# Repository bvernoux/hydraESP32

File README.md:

# hydraESP32

HydraESP32 HydraBus v1.0 Shield for ESP-WROOM-32 V1.1 Rev1.0 (Tested) 

https://oshpark.com/shared_projects/dgKJqznH

HydraBus Shield / Breakout board for ESP-WROOM-32 or ESP-32S.

This shield can be used with or without HydraBus board, you can even cut HydraBus specific right side (on the line) to have a tiny ESP-WROOM-32 breakout board.

It is not mandatory to solder the components on this shield in order to use it, you will just need to connect +3v3 on VCC Pin header 

* New features versus previous version [V1.0 Rev1.1](https://oshpark.com/shared_projects/6t5hURXL):
   * Added LDO (TPS73633DBVR SOT23-5) to convert 5V(VUSB) to a clean VCC (+3.3v) for ESP32 and which can be enabled by an HydraBus Pin or  with a JUMPER on J7 (which connect +3.3V from HydraBus to EN of the LDO)
   * Added VCC connector in order to measure ESP32 current/power consumption (if not used to measure current just add a JUMPER on VCC to power the ESP32)
   * Added J6 connector to have access to ESP32 SPI FLASH IOs (now all pins are available)

* This shield can be used only on bottom of HydraBus board (in order to use other shields on top of HydraBus)

* The [HydraBus board](http://hydrabus.com/hydrabus-1-0-specifications/) is a small (60mm x 37mm) and [low cost](http://hydrabus.com/buy-online/), multi-tool extensible board with STM32F405 Cortex M4F 32bits MCU @168MHz with a fully open source firmware [hydrafw](https://github.com/bvernoux/hydrafw) and full online documentation [hydrafw wiki](https://github.com/bvernoux/hydrafw/wiki)

* The ESP-WROOM-32 is a low-power 32-bit 240 MHz dual core MCU Wi-
Fi+BLE combo module that highly integrates TCP/IP network stacks, 12-
bit ADC and HSPI/SDIO/UART/PWM/I2C/I2S interfaces.
See [ESP32 Overview](http://www.espressif.com/en/products/hardware/esp32/overview), [ESP-WROOM-32 link/info](https://espressif.com/en/producttype/esp-wroom-32), [Espressif Products Overview including ESP-WROOM-32 PDF](http://www.elinistech.com/images/esp8266/Espressif%20Introduction-EN.pdf)

* Design based on official [esp_wroom_32_datasheet_en.pdf (September 26, 2016)](https://espressif.com/sites/default/files/documentation/esp_wroom_32_datasheet_en.pdf)

BOM:

| Qty | Value | Device | Package | Parts | Description |
|------|----------|------------|-------------|---------|------------------|
| 1   | -        | ESP_WROOM_32 or ESP-32S        | ESP-WROOM-32 or ESP-32S          | U1        | Espressif ESP-WROOM-32 or ESP-32S Module    |
| 1   | -        | TPS73633 | SOT23-5L              | U2        | Texas Instrument LDO             |
| 1   | 2.2uF    | CAPACITOR_NPOL-0603 | C603                  | C1        | SMD Non-Polarized capacitor          |
| 1   | 1uF      | CAPACITOR_NPOL-0603 | C603                  | C2        | SMD Non-Polarized capacitor          |
| 2   | 100nF    | CAPACITOR_NPOL-0603 | C603                  | C3, C4    | SMD Non-Polarized capacitor          |
| 2   | 10K      | RESISTOR-0603       | R603                  | R1, R2    | SMD Resistor                                 |
| 1   | -        |                     | HYDRABUS_SHIELD_M2X7  | J1        | 2x7 Pin header      |
| 4   | -        |                     | HYDRABUS_SHIELD_M2X10 |J2, J3, J4, J5    | 2x10 Pin header                  |
| 2   | -        |                     | HYDRABUS_SHIELD_M1X6  | J6, SWD_DEBUG | 1x6 Pin header |
| 2   | -        |                     | Jumper - 2 Pin  | J7, VCC   |  Jumper 2 Pin |
| 2   | -        |                     | CON_HEADER_1X02-PTH   | J7, VCC   | 1x2 Pin header |

Note1: LDO U2 can be also replaced by MIC5319-3.3YD5-TR (Microchip)

Note2: If you do not want to solder those components you can avoid them and directly connect HydraBus 3v3 to VCC Pin near J5 marking

For more details see also [HydraBus_1_0_Shield_ESP_WROOM_32_v1_1_Rev1_BOM.csv](HydraBus_1_0_Shield_ESP_WROOM_32_v1_1_Rev1_BOM.csv)

Tested with success with an ESP-32S Module from Ai-Thinker (it is recommended to use official Espressif ESP-WROOM-32)

HydraBus_1_0_Shield_ESP_WROOM_32_v1_1_Rev1_Top:
[HydraBus_1_0_Shield_ESP_WROOM_32_v1_1_Rev1_Top](HydraBus_1_0_Shield_ESP_WROOM_32_v1_1_Rev1_Top.png)

HydraBus_1_0_Shield_ESP_WROOM_32_v1_1_Rev1_Bottom:
[HydraBus_1_0_Shield_ESP_WROOM_32_v1_1_Rev1_Bottom](HydraBus_1_0_Shield_ESP_WROOM_32_v1_1_Rev1_Bottom.png)

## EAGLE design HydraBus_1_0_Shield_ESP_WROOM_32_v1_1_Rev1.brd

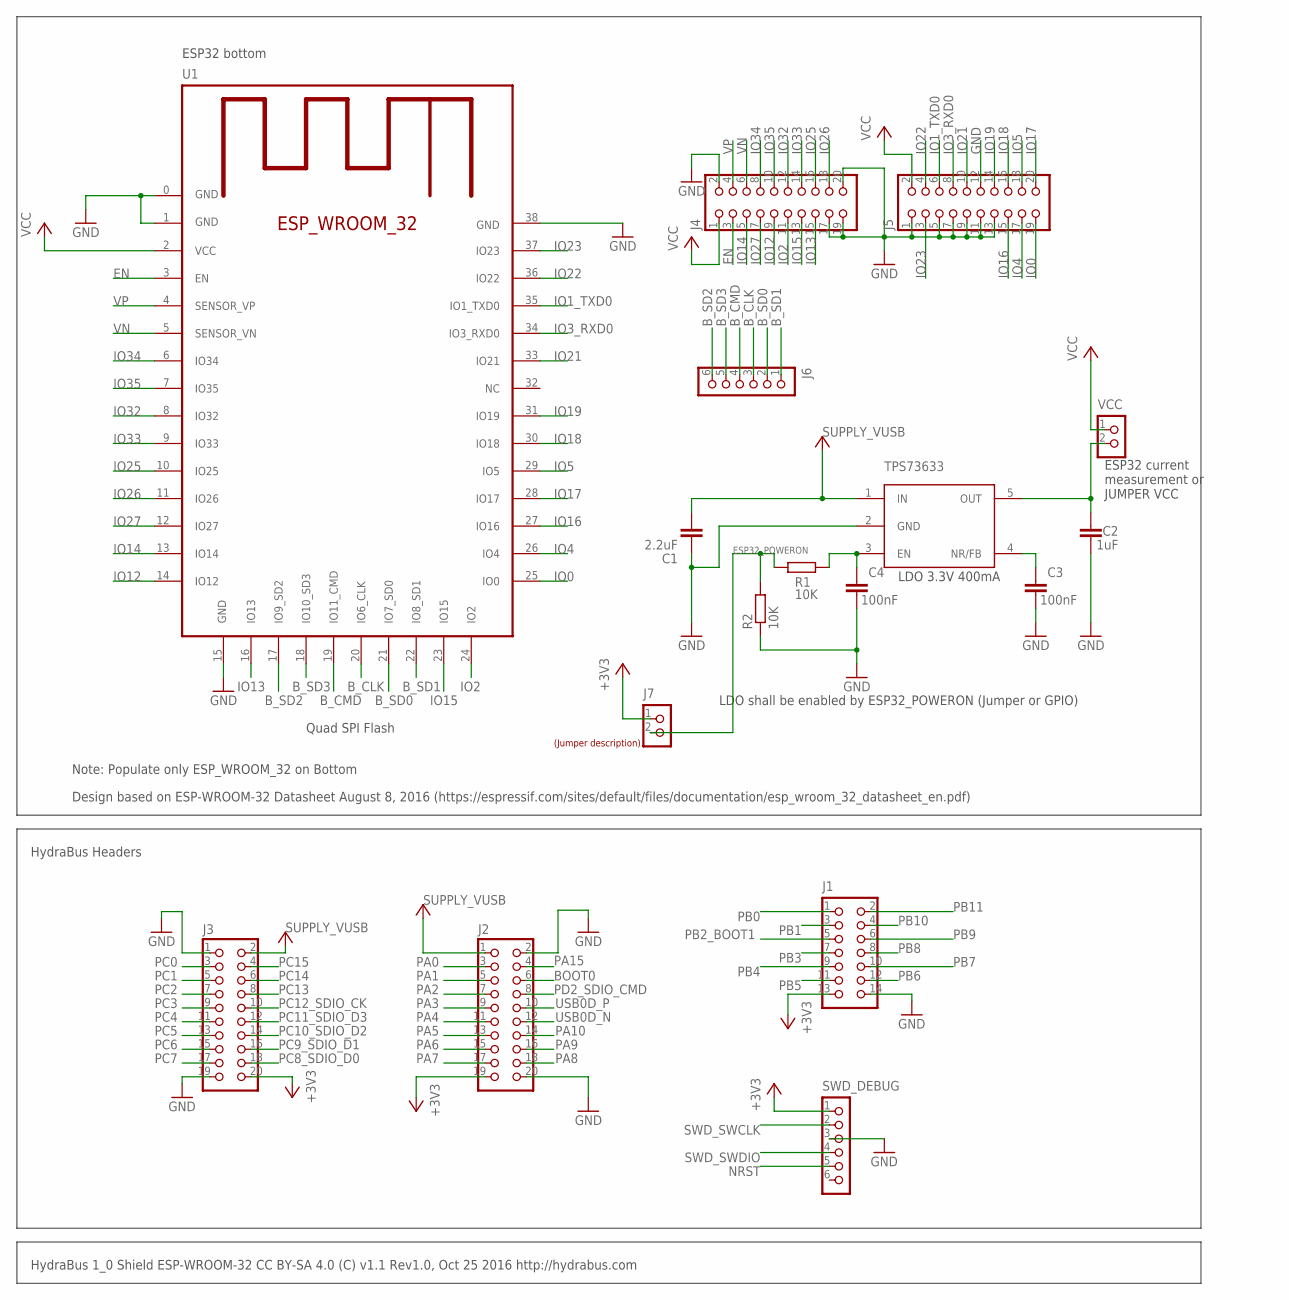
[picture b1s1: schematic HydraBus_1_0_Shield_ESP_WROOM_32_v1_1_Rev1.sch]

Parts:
C1: 2.2uF; C603
C2: 1uF; C603
C3, C4: 100nF; C603
J1: HYDRABUS_SHIELD_CON_HEADER_2X07_BOTTOM; HYDRABUS_SHIELD_M2X7_BOTTOM
J2, J3: HYDRABUS_SHIELD_CON_HEADER_2X10_BOTTOM; HYDRABUS_SHIELD_M2X10_BOTTOM
J4, J5: HYDRABUS_SHIELD_CON_HEADER_2X10; HYDRABUS_SHIELD_M2X10
J6: HYDRABUS_SHIELD_CON_HEADER_1X06; HYDRABUS_SHIELD_M1X6
J7: CON_HEADER_1X02-PTH; M1X2
R1, R2: 10K; R603
SWD_DEBUG: HYDRABUS_SHIELD_CON_HEADER_1X06_BOTTOM; HYDRABUS_SHIELD_M1X6_BOTTOM
U1: ESP_WROOM_32
U2: TPS73633; SOT23-5L
U$1: LABEL_JUMPER_1X2; JUMP2_DESC
VCC: CON_HEADER_1X02-PTH; M1X2

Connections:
+3V3: J1.13, J2.19, J3.20, J7.1, SWD_DEBUG.1
BOOT0: J2.6
B_CLK: J6.3, U1.20 (IO6_CLK)
B_CMD: J6.4, U1.19 (IO11_CMD)
B_SD0: J6.2, U1.21 (IO7_SD0)
B_SD1: J6.1, U1.22 (IO8_SD1)
B_SD2: J6.6, U1.17 (IO9_SD2)
B_SD3: J6.5, U1.18 (IO10_SD3)
EN: J4.3, U1.3 (EN)
ESP32_POWERON: J7.2, R1.1, R2.2
GND: C1.1, C2.1, C3.1, C4.1, J1.14, J2.2, J2.20, J3.1, J3.19, J4.2, J4.17, J4.19, J4.20, J5.1, J5.5, J5.7, J5.9, J5.11, J5.12, J5.13, R2.1, SWD_DEBUG.3, U1.0 (GND), U1.1 (GND), U1.15 (GND), U1.38 (GND), U2.2 (GND)
IO0: J5.19, U1.25 (IO0)
IO1_TXD0: J5.6, U1.35 (IO1_TXD0)
IO2: J4.11, U1.24 (IO2)
IO3_RXD0: J5.8, U1.34 (IO3_RXD0)
IO4: J5.17, U1.26 (IO4)
IO5: J5.18, U1.29 (IO5)
IO12: J4.9, U1.14 (IO12)
IO13: J4.15, U1.16 (IO13)
IO14: J4.5, U1.13 (IO14)
IO15: J4.13, U1.23 (IO15)
IO16: J5.15, U1.27 (IO16)
IO17: J5.20, U1.28 (IO17)
IO18: J5.16, U1.30 (IO18)
IO19: J5.14, U1.31 (IO19)
IO21: J5.10, U1.33 (IO21)
IO22: J5.4, U1.36 (IO22)
IO23: J5.3, U1.37 (IO23)
IO25: J4.16, U1.10 (IO25)
IO26: J4.18, U1.11 (IO26)
IO27: J4.7, U1.12 (IO27)
IO32: J4.12, U1.8 (IO32)
IO33: J4.14, U1.9 (IO33)
IO34: J4.8, U1.6 (IO34)
IO35: J4.10, U1.7 (IO35)
unnamed: C3.2, U2.4 (NR/FB)
unnamed: C4.2, R1.2, U2.3 (EN)
unnamed: C2.2, U2.5 (OUT), VCC.2
NRST: SWD_DEBUG.5
PA0: J2.3
PA1: J2.5
PA2: J2.7
PA3: J2.9
PA4: J2.11
PA5: J2.13
PA6: J2.15
PA7: J2.17
PA8: J2.18
PA9: J2.16
PA10: J2.14
PA15: J2.4
PB0: J1.1
PB1: J1.3
PB2_BOOT1: J1.5
PB3: J1.7
PB4: J1.9
PB5: J1.11
PB6: J1.12
PB7: J1.10
PB8: J1.8
PB9: J1.6
PB10: J1.4
PB11: J1.2
PC0: J3.3
PC1: J3.5
PC2: J3.7
PC3: J3.9
PC4: J3.11
PC5: J3.13
PC6: J3.15
PC7: J3.17
PC8_SDIO_D0: J3.18
PC9_SDIO_D1: J3.16
PC10_SDIO_D2: J3.14
PC11_SDIO_D3: J3.12
PC12_SDIO_CK: J3.10
PC13: J3.8
PC14: J3.6
PC15: J3.4
PD2_SDIO_CMD: J2.8
SWD_SWCLK: SWD_DEBUG.2
SWD_SWDIO: SWD_DEBUG.4
USB0D_N: J2.12
USB0D_P: J2.10
VCC: J4.1, J5.2, U1.2 (VCC), VCC.1
VN: J4.6, U1.5 (SENSOR_VN)
VP: J4.4, U1.4 (SENSOR_VP)
VUSB: C1.2, J2.1, J3.2, U2.1 (IN)

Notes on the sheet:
HydraBus 1_0 Shield ESP-WROOM-32 CC BY-SA 4.0 (C) v1.1 Rev1.0, Oct 25 2016 http://hydrabus.com
HydraBus Headers
ESP32 bottom
Note: Populate only ESP_WROOM_32 on Bottom
Quad SPI Flash
Design based on ESP-WROOM-32 Datasheet August 8, 2016 (https://espressif.com/sites/default/files/documentation/esp_wroom_32_datasheet_en.pdf)
LDO 3.3V 400mA
LDO shall be enabled by ESP32_POWERON (Jumper or GPIO)
ESP32 current measurement or JUMPER VCC

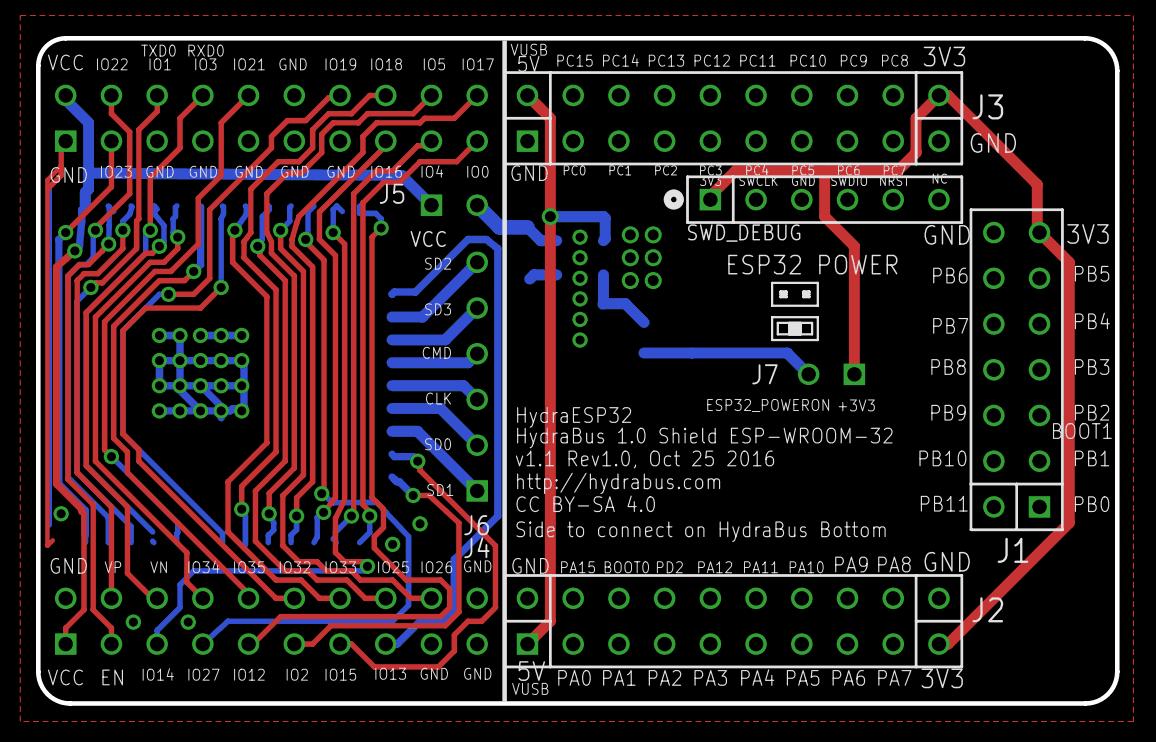
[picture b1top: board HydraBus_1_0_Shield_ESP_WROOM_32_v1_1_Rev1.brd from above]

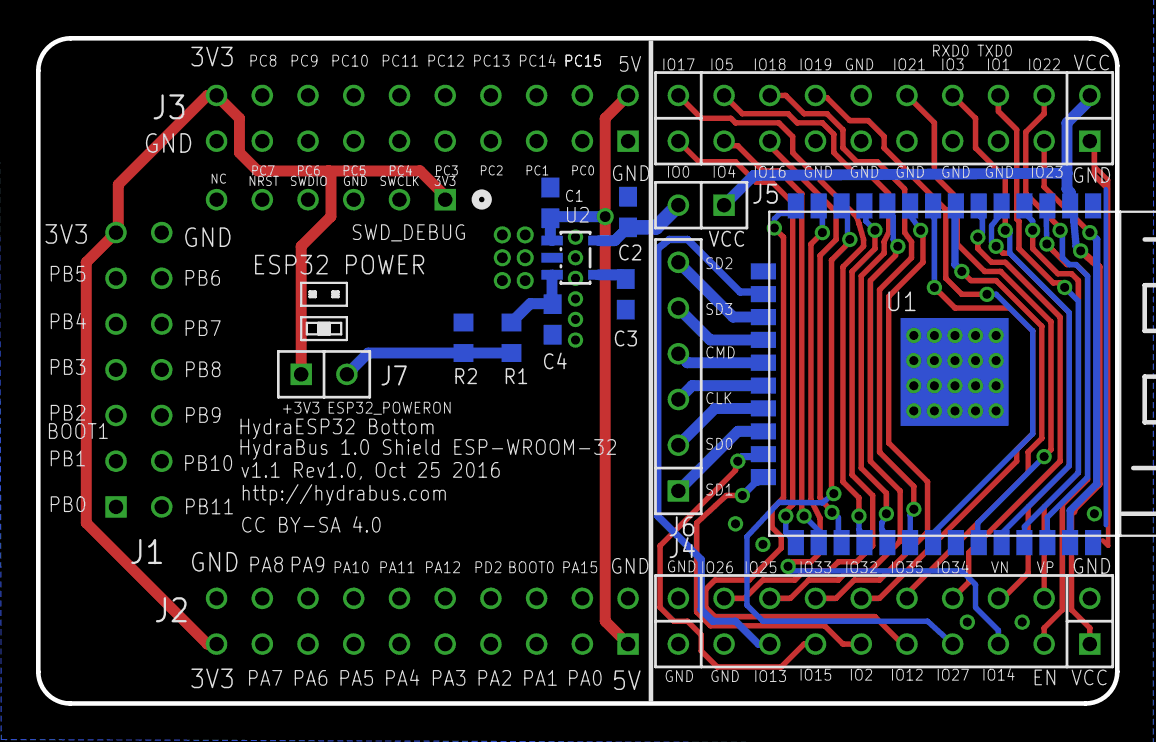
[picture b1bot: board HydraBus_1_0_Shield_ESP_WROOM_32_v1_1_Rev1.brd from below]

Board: 2 copper layers, 59.9 x 37.0 mm, 19 parts (11 on the bottom side), 41 nets.

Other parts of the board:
U$2: LABEL_JUMPER_1X2; JUMP2_DESC

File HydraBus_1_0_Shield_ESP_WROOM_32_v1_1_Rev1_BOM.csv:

Qty,Value,Device,Package,Parts,Description
1,-,ESP_WROOM_32,ESP_WROOM_32,U1,ESP_WROOM_32 Module 09 Aug 2016
2,100nF,CAPACITOR_NPOL-0603,C603,"C3, C4",Non-Polarized capacitor in various packages
2,10K,RESISTOR-0603,R603,"R1, R2",
1,1uF,CAPACITOR_NPOL-0603,C603,C2,Non-Polarized capacitor in various packages
1,2.2uF,CAPACITOR_NPOL-0603,C603,C1,Non-Polarized capacitor in various packages
2,CON_HEADER_1X02-PTH,CON_HEADER_1X02-PTH,M1X2,"J7, VCC",
1,HYDRABUS_SHIELD_CON_HEADER_1X06,HYDRABUS_SHIELD_CON_HEADER_1X06,HYDRABUS_SHIELD_M1X6,J6,SWD Header 1x6 Pin header
1,HYDRABUS_SHIELD_CON_HEADER_1X06_BOTTOM,HYDRABUS_SHIELD_CON_HEADER_1X06_BOTTOM,HYDRABUS_SHIELD_M1X6_BOTTOM,SWD_DEBUG,SWD Header 1x6 Pin header bottom
1,HYDRABUS_SHIELD_CON_HEADER_2X07_BOTTOM,HYDRABUS_SHIELD_CON_HEADER_2X07_BOTTOM,HYDRABUS_SHIELD_M2X7_BOTTOM,J1,2x7 Pin header bottom
2,HYDRABUS_SHIELD_CON_HEADER_2X10,HYDRABUS_SHIELD_CON_HEADER_2X10,HYDRABUS_SHIELD_M2X10,"J4, J5",2x10 Pin header
2,HYDRABUS_SHIELD_CON_HEADER_2X10_BOTTOM,HYDRABUS_SHIELD_CON_HEADER_2X10_BOTTOM,HYDRABUS_SHIELD_M2X10_BOTTOM,"J2, J3",2x10 Pin header bottom
1,TPS73633,TPS73633,SOT23-5L,U2,Texas Instrument LDO

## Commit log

2017-10-05 Add Eagle 7.x files, BOM, Schematic
